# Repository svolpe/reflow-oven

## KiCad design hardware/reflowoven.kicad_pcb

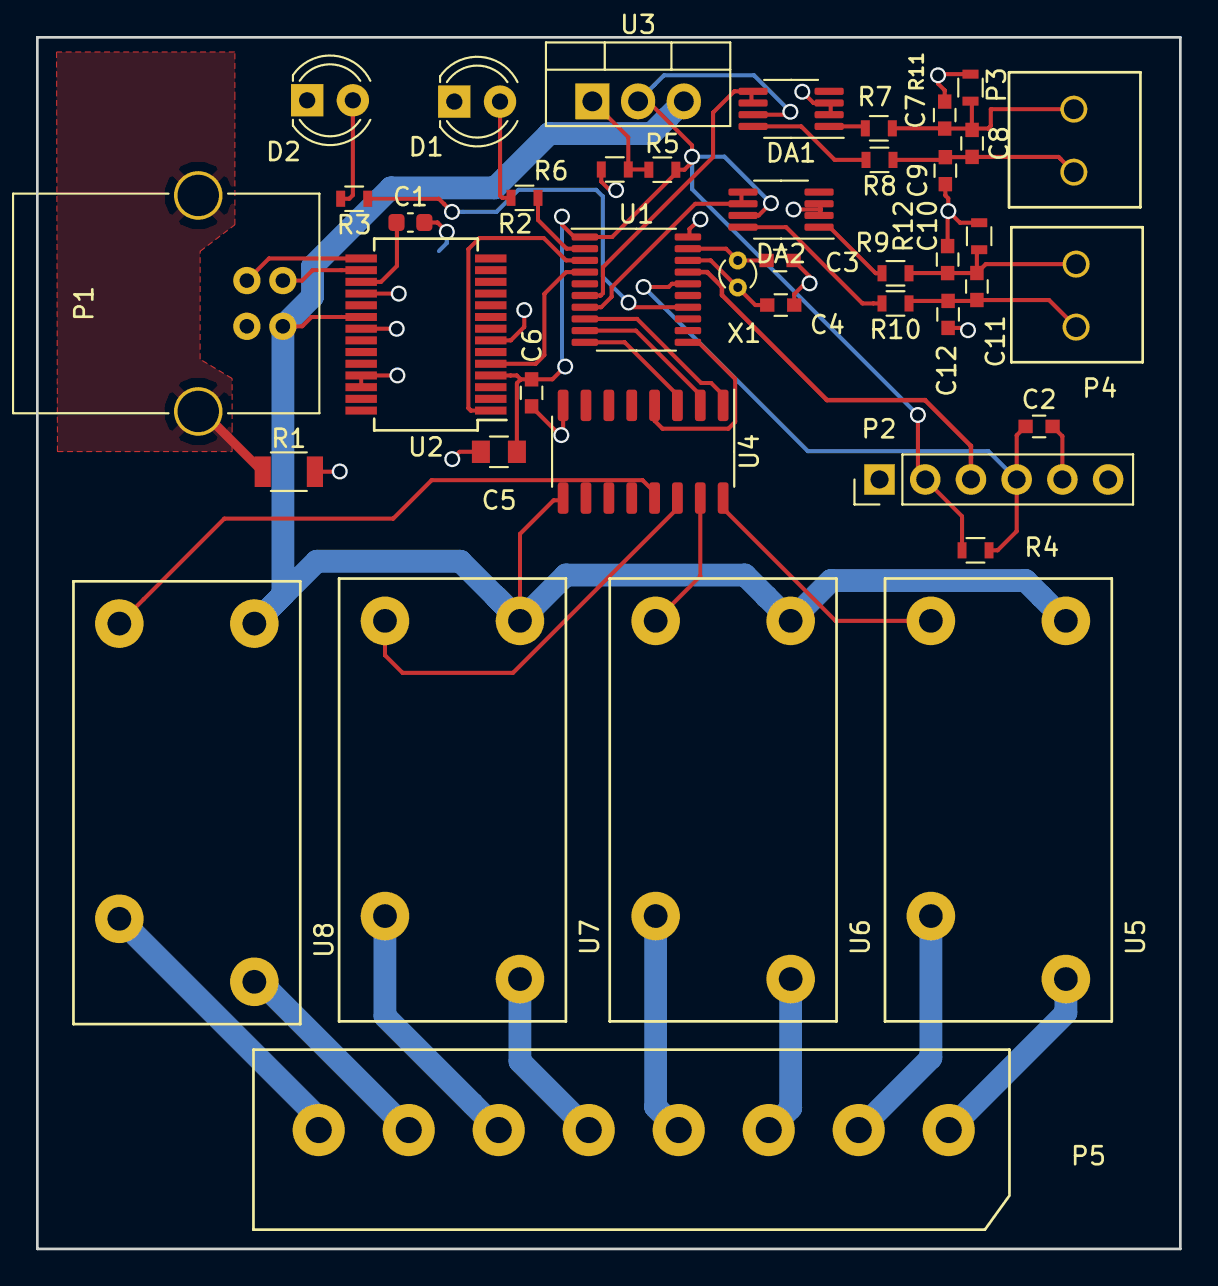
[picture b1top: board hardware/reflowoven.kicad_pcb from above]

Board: 2 copper layers, 63.5 x 67.3 mm, 42 parts (0 on the bottom side), 44 nets.

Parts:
C1: 100nF; C_0603_1608Metric
C2: 1nF; C_0603
C3, C4: 12pF; C_0603
C5: 10uF; C_0805
C6, C8, C11: 100nF; C_0603
C7, C9, C10, C12: 10nF; C_0603
D1, D2: LED; LED_D4.0mm
DA1, DA2: AD8495; MSOP-8_3x3mm_P0.65mm
P1: USB-A-SHLD; USB_B
P2: CONN_6; Pin_Header_Straight_1x06_Pitch2.54mm
P3, P4: CONN_2; 1751248
P5: CONN_01X08; 1935226
R1: 0; R_1206
R2, R3: 270; R_0603
R4: 47K; R_0603
R5: 750; R_0603
R6: 2K; R_0603
R7, R8, R9, R10: 10K; R_0603
R11, R12: 1M; R_0603
U1: MSP430G2553IPW20; TSSOP-20_4.4x6.5mm_P0.65mm
U2: FT232RL; SSOP-28_5.3x10.2mm_P0.65mm
U3: LM317; TO-220-3_Vertical
U4: ULN2003A; SO-16_3.9x9.9mm_P1.27mm
U5, U6, U7, U8: MCHRM3H
X1: CRYSTAL; Crystal_Round_d1.0mm_Vertical

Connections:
+3V3: C5.1, C6.1, DA1.7 (+Vs), DA2.7 (+Vs), P2.2, R4.1, R5.2, U1.1 (DVCC), U2.4 (VCCIO), U3.2 (VO)
+5V: P1.1 (VBUS), U2.20 (VCC), U3.3 (VI), U4.9 (COM), U5.1, U6.1, U7.1, U8.1
/ESD_RING: P1.5 (Shield), R1.1
/P1.0: R2.1, U1.2 (TA0CLK/ACLK/CA0/A0/P1.0)
/P1.6: R3.1, U1.14 (TDI/TCLK/UCB0SOMI/UCB0SCL/TA0.1/CA6/A6/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)
/RX: U1.3 (UCA0RXD/UCA0SOMI/TA0.0/CA1/A1/P1.1), U2.1 (TXD)
/Relays and Themocouples/RelayCTRL_1: U1.8 (P2.0/TA1.0), U4.1 (I1)
/Relays and Themocouples/RelayCTRL_2: U1.9 (P2.1/TA1.1), U4.2 (I2)
/Relays and Themocouples/RelayCTRL_3: U1.10 (P2.2/TA1.1), U4.3 (I3)
/Relays and Themocouples/RelayCTRL_4: U1.11 (P2.3/TA1.0), U4.4 (I4)
/Relays and Themocouples/Relay_1_Term_A: P5.1, U5.3
/Relays and Themocouples/Relay_1_Term_B: P5.2, U5.4
/Relays and Themocouples/Relay_2_Term_A: P5.3, U6.3
/Relays and Themocouples/Relay_2_Term_B: P5.4, U6.4
/Relays and Themocouples/Relay_3_Term_A: P5.5, U7.3
/Relays and Themocouples/Relay_3_Term_B: P5.6, U7.4
/Relays and Themocouples/Relay_4_Term_A: P5.7, U8.3
/Relays and Themocouples/Relay_4_Term_B: P5.8, U8.4
/Relays and Themocouples/Thermocouple_1+: C8.2, C9.1, P3.1, R8.1
/Relays and Themocouples/Thermocouple_1-: C7.2, C8.1, P3.2, R7.1, R11.1
/Relays and Themocouples/Thermocouple_2+: C11.2, C12.1, P4.1, R10.1
/Relays and Themocouples/Thermocouple_2-: C10.2, C11.1, P4.2, R9.1, R12.1
/TCK: P2.3, U1.17 (TEST/SBWTCK)
/TDIO: C2.1, P2.4, R4.2, U1.16 (~RST/NMI/SBWTDIO)
/TEMP_1: DA1.5 (SENSE), DA1.6
/TEMP_2: DA2.5 (SENSE), DA2.6
/TX: U1.4 (UCA0TXD/UCA0SIMO/TA0.1/CA2/A2/P1.2), U2.5 (RXD)
/USB_DM: P1.3 (D+), U2.15 (USBD+)
/USB_DP: P1.2 (D-), U2.16 (USBD-)
/XIN: C3.1, U1.19 (P2.6/XIN/TA0.1), X1.2
/XOUT: C4.1, U1.18 (P2.7/XOUT), X1.1
GND: C1.1, C2.2, C3.2, C4.2, C5.2, C6.2, C7.1, C9.2, C10.1, C12.2, D1.1 (A), D2.1 (A), DA1.2 (REF), DA1.3 (-Vs), DA2.2 (REF), DA2.3 (-Vs), P1.4 (GND), P2.5, R1.2, R6.1, R11.2, R12.2, U1.20 (DVSS), U2.7 (GND), U2.18 (GND), U2.21 (GND), U2.25 (AGND), U4.8 (GND)
unnamed: C1.2, U2.17 (3V3OUT)
unnamed: D1.2 (K), R2.2
unnamed: D2.2 (K), R3.2
unnamed: DA1.1 (-IN), R7.2
unnamed: DA1.8 (+IN), R8.2
unnamed: DA2.1 (-IN), R9.2
unnamed: DA2.8 (+IN), R10.2
unnamed: R5.1, R6.2, U3.1 (ADJ)
unnamed: U4.13 (O4), U8.2
unnamed: U4.14 (O3), U7.2
unnamed: U4.15 (O2), U6.2
unnamed: U4.16 (O1), U5.2

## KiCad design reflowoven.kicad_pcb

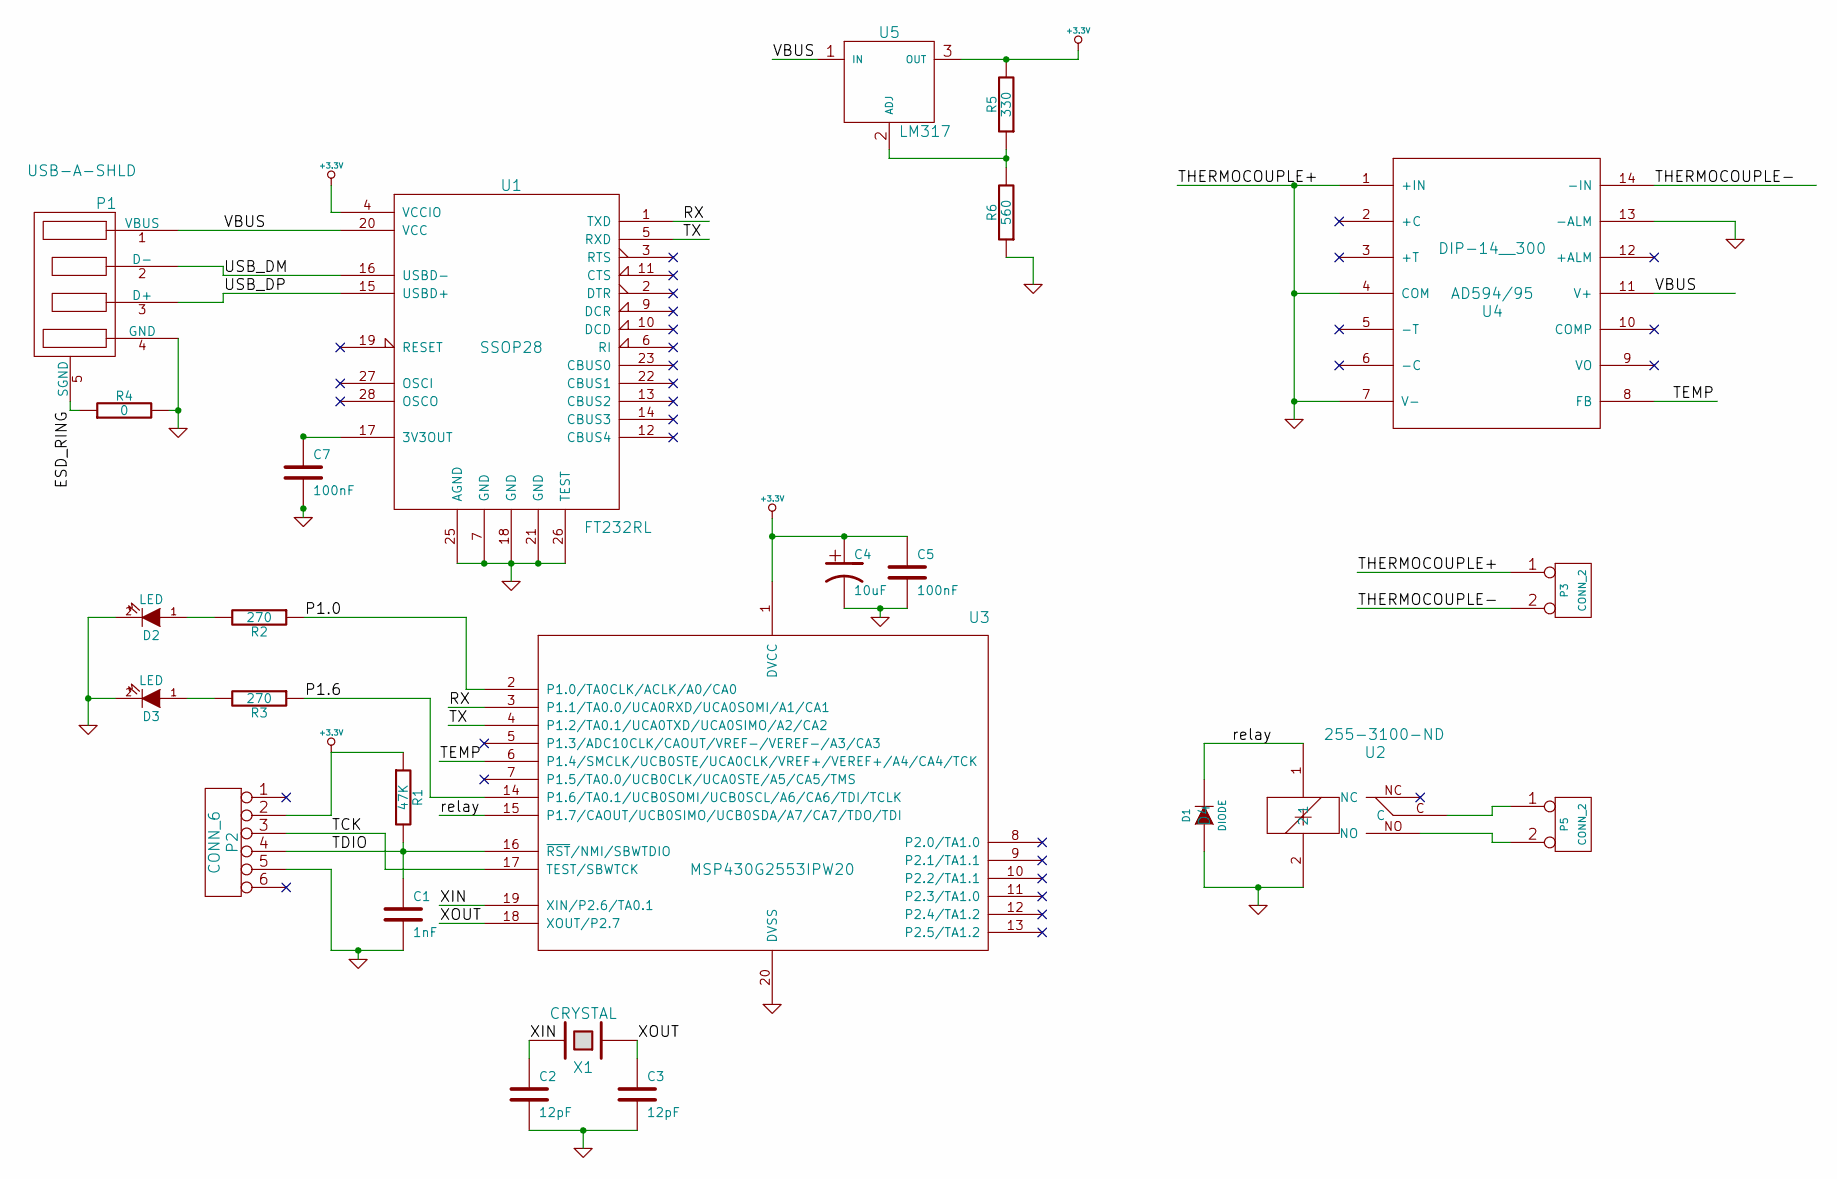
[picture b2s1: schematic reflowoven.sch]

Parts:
C1: 1nF
C2, C3: 12pF
C4: 10uF
C5, C7: 100nF
D1: DIODE; D4
D2, D3: LED
P1: USB-A-SHLD
P2: CONN_6
P3, P5: CONN_2
R1: 47K
R2, R3: 270
R4: 0
R5: 330
R6: 560
U1: FT232RL; SSOP28
U2: 255-3100-ND
U3: MSP430G2553IPW20
U4: AD594/95; DIP-14__300
U5: LM317
X1: CRYSTAL

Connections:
+3.3V: C4.1, C5.1, P2.2, R1.1, R5.2, U1.4 (VCCIO), U3.1 (DVCC), U5.3 (OUT)
/ESD_RING: P1.5 (SGND), R4.1
/P1.0: R2.1, U3.2 (P1.0/TA0CLK/ACLK/A0/CA0)
/P1.6: R3.1, U3.14 (P1.6/TA0.1/UCB0SOMI/UCB0SCL/A6/CA6/TDI/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)
/RX: U1.1 (TXD), U3.3 (P1.1/TA0.0/UCA0RXD/UCA0SOMI/A1/CA1)
/TCK: C1.1, P2.4, R1.2, U3.16 (~RST~/NMI/SBWTDIO)
/TDIO: P2.3, U3.17 (TEST/SBWTCK)
/TEMP: U3.6 (P1.4/SMCLK/UCB0STE/UCA0CLK/VREF+/VEREF+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), U4.8 (FB)
/THERMOCOUPLE-: P3.2 (PM), U4.14 (-IN)
/TX: U1.5 (RXD), U3.4 (P1.2/TA0.1/UCA0TXD/UCA0SIMO/A2/CA2)
/USB_DM: P1.2 (D-), U1.16 (USBD-)
/USB_DP: P1.3 (D+), U1.15 (USBD+)
/VBUS: P1.1 (VBUS), U1.20 (VCC), U4.11 (V+), U5.1 (IN)
/XIN: C2.1, U3.19 (XIN/P2.6/TA0.1), X1.2
/XOUT: C3.1, U3.18 (XOUT/P2.7), X1.1
/relay: D1.2 (K), U2.1, U3.15 (P1.7/CAOUT/UCB0SIMO/UCB0SDA/A7/CA7/TDO/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)
GND: C1.2, C2.2, C3.2, C4.2, C5.2, C7.2, D1.1 (A), D2.2 (K), D3.2 (K), P1.4 (GND), P2.5, P3.1, R4.2, R6.1, U1.7 (GND), U1.18 (GND), U1.21 (GND), U1.25 (AGND), U1.26 (TEST), U2.2, U3.20 (DVSS), U4.1 (+IN), U4.4 (COM), U4.7 (V-), U4.13 (-ALM)
unnamed: R5.1, R6.2, U5.2 (ADJ)
unnamed: C7.1, U1.17 (3V3OUT)
unnamed: P5.2 (PM), U2.NO
unnamed: P5.1, U2.C
unnamed: D2.1 (A), R2.2
unnamed: D3.1 (A), R3.2

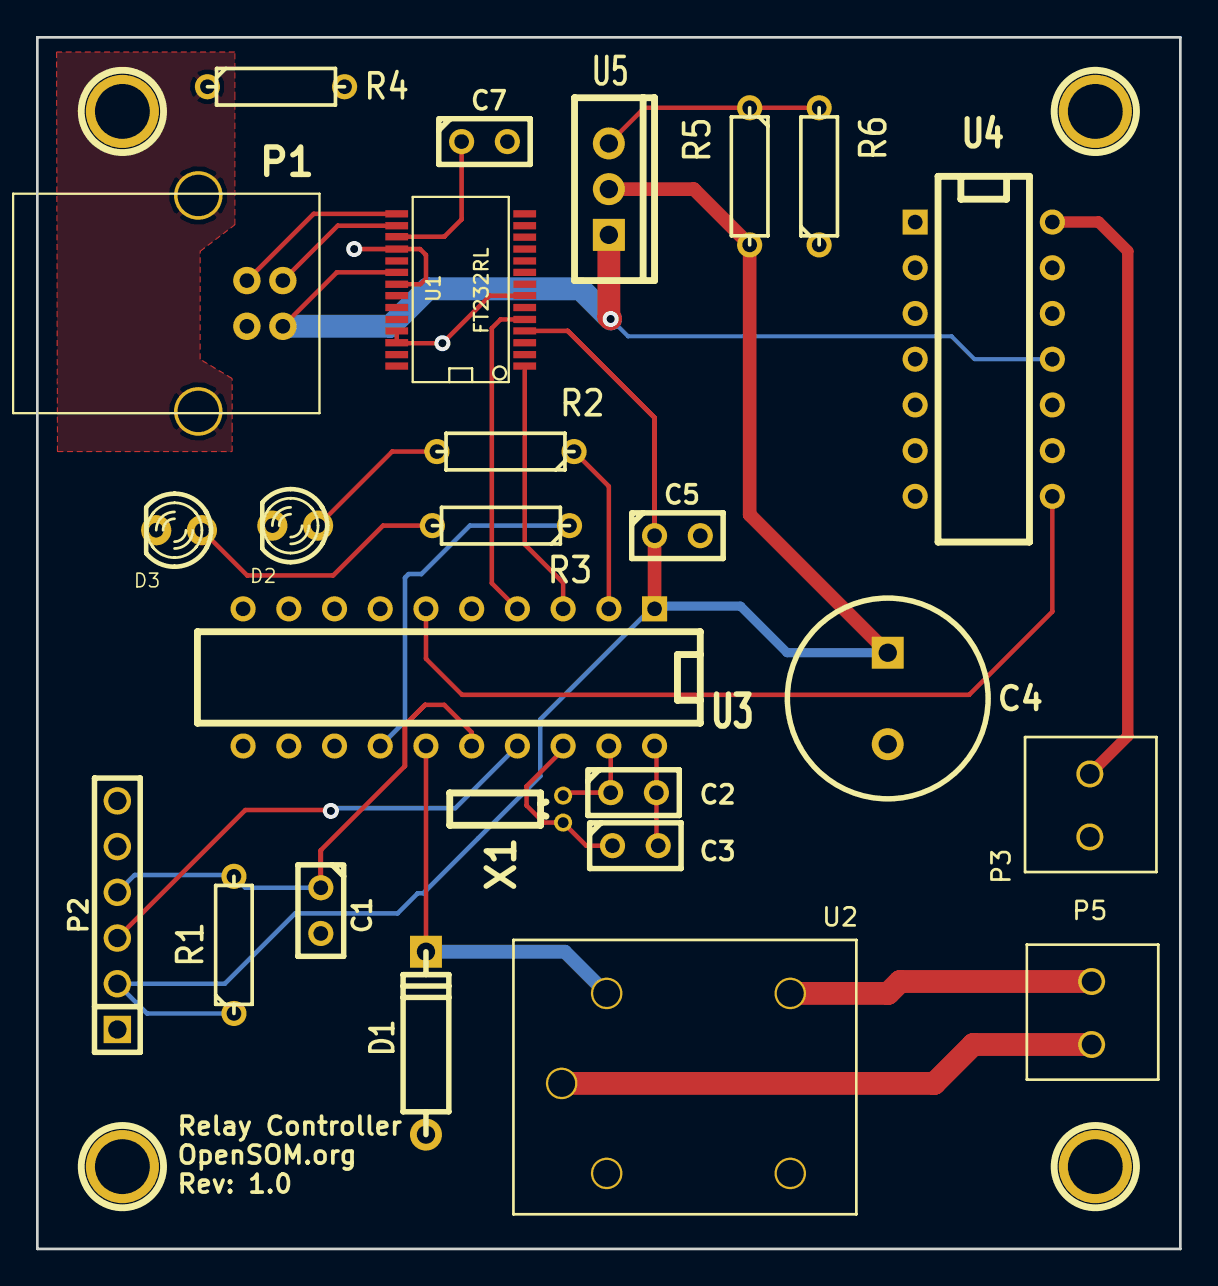
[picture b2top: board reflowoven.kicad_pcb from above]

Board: 2 copper layers, 63.5 x 67.3 mm, 29 parts (0 on the bottom side), 23 nets.

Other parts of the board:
1PIN, 1PIN#2, 1PIN#3, 1PIN#4: P***; 1pin

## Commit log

2017-04-09 Initial checkin
2017-04-09 Reorganize source code directory structure
2017-04-09 Move hardware files into hardware folder
2017-04-09 First round of changes to add additional relays and thermal couples
2017-04-09 Finalized layout with 2 thermocouples and 4 relays
2017-04-09 Add gerber files
2017-04-09 cleaned up schematic some
2017-04-09 Update schematic to reflect proper resistor values for 3.3V regulator
2017-04-09 Update MSP430 design to have a more advanced command handler capable of taking arguments.
2017-04-09 Fixed wireing of LM317 - schematic footprint pinout was incorrect
2017-04-09 Change thermocouple circuitry from 5V to 3.3V
2017-04-09 Update PCB to change thermocouples to 3.3V. Update command interface to convert temp to degrees instead of sending raw ADC
2017-04-10 Update schematic and PCB to include additional 1M ohm resitor on thermocouple - term. This seems to stablize the temp readings.
2022-01-14 initial checkin of KiCAD v6.0 design files converted from old KiCAD
2022-01-14 Updated schematic and PCB to 100% match footprints
